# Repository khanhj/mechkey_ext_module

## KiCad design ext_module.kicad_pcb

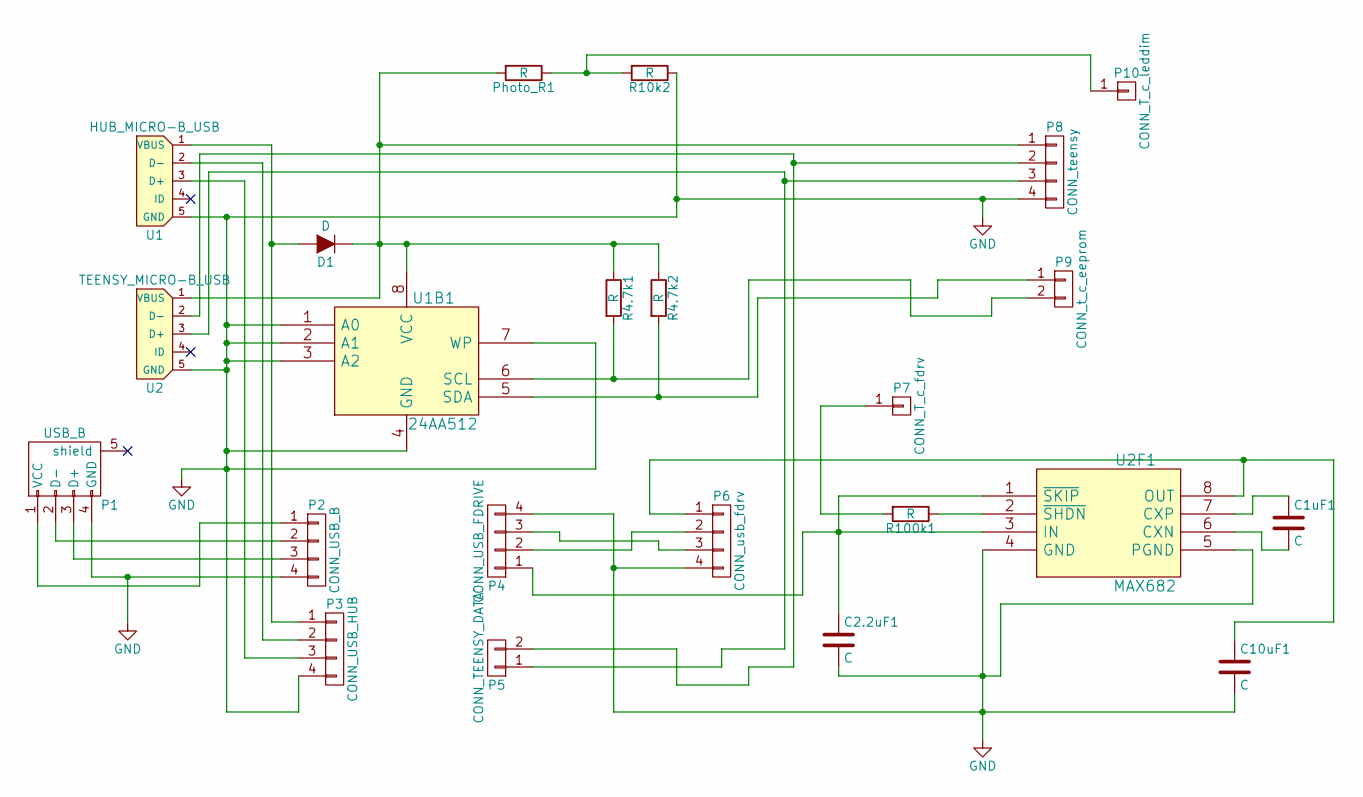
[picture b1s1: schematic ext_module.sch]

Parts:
C1uF1, C2.2uF1, C10uF1: C; C_0805
D1: D; D_A-405_P7.62mm_Horizontal
P1: USB_B; USB_A
P2: CONN_USB_B; Pin_Header_Straight_1x04_Pitch2.54mm
P3: CONN_USB_HUB; Pin_Header_Straight_1x04_Pitch2.54mm
P4: CONN_USB_FDRIVE; Pin_Header_Straight_1x04_Pitch2.54mm
P5: CONN_TEENSY_DATA; Pin_Header_Straight_1x02_Pitch2.54mm
P6: CONN_usb_fdrv; Pin_Header_Straight_1x04_Pitch2.54mm
P7: CONN_T_c_fdrv; Pin_Header_Straight_1x01_Pitch2.54mm
P8: CONN_teensy; Pin_Header_Straight_1x04_Pitch2.54mm
P9: CONN_t_c_eeprom; Pin_Header_Straight_1x02_Pitch2.54mm
P10: CONN_T_c_leddim; Pin_Header_Straight_1x01_Pitch2.54mm
Photo_R1: R; Pin_Header_Angled_1x02_Pitch2.54mm
R4.7k1, R4.7k2, R10k2, R100k1: R; R_0805
U1: HUB_MICRO-B_USB; USB_Micro-B
U1B1: 24AA512; SOIC-8-N
U2: TEENSY_MICRO-B_USB; USB_Micro-B
U2F1: MAX682; SOIC-8-N

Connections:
GND: C2.2uF1.2, C10uF1.2, P1.4 (GND), P2.4, P3.4, P4.4, P6.4, P8.4, R10k2.1, U1.5 (GND), U1B1.1 (A0), U1B1.2 (A1), U1B1.3 (A2), U1B1.4 (GND), U1B1.7 (WP), U2.5 (GND), U2F1.4 (GND), U2F1.5 (PGND)
unnamed: C1uF1.1, U2F1.7 (CXP)
unnamed: C1uF1.2, U2F1.6 (CXN)
unnamed: C2.2uF1.1, P4.1, U2F1.1 (~SKIP), U2F1.3 (IN)
unnamed: C10uF1.1, P6.1, U2F1.8 (OUT)
unnamed: D1.1 (K), P8.1, Photo_R1.2, R4.7k1.1, R4.7k2.1, U1B1.8 (VCC), U2.1 (VBUS)
unnamed: D1.2 (A), P3.1, U1.1 (VBUS)
unnamed: P1.1 (VCC), P2.1
unnamed: P1.2 (D-), P2.2
unnamed: P1.3 (D+), P2.3
unnamed: P3.2, U1.2 (D-)
unnamed: P3.3, U1.3 (D+)
unnamed: P4.2, P6.2
unnamed: P4.3, P6.3
unnamed: P5.1, P8.3, U2.3 (D+)
unnamed: P5.2, P8.2, U2.2 (D-)
unnamed: P7.1, R100k1.2
unnamed: P9.1, R4.7k2.2, U1B1.5 (SDA)
unnamed: P9.2, R4.7k1.2, U1B1.6 (SCL)
unnamed: P10.1, Photo_R1.1, R10k2.2
unnamed: R100k1.1, U2F1.2 (~SHDN)

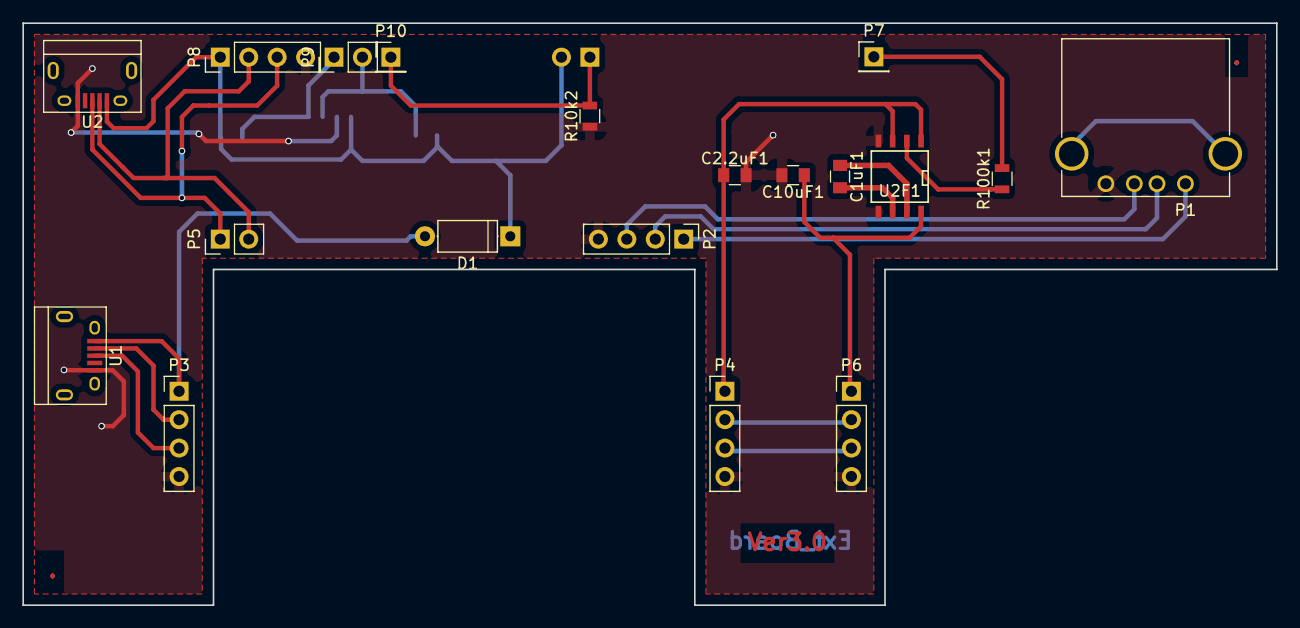
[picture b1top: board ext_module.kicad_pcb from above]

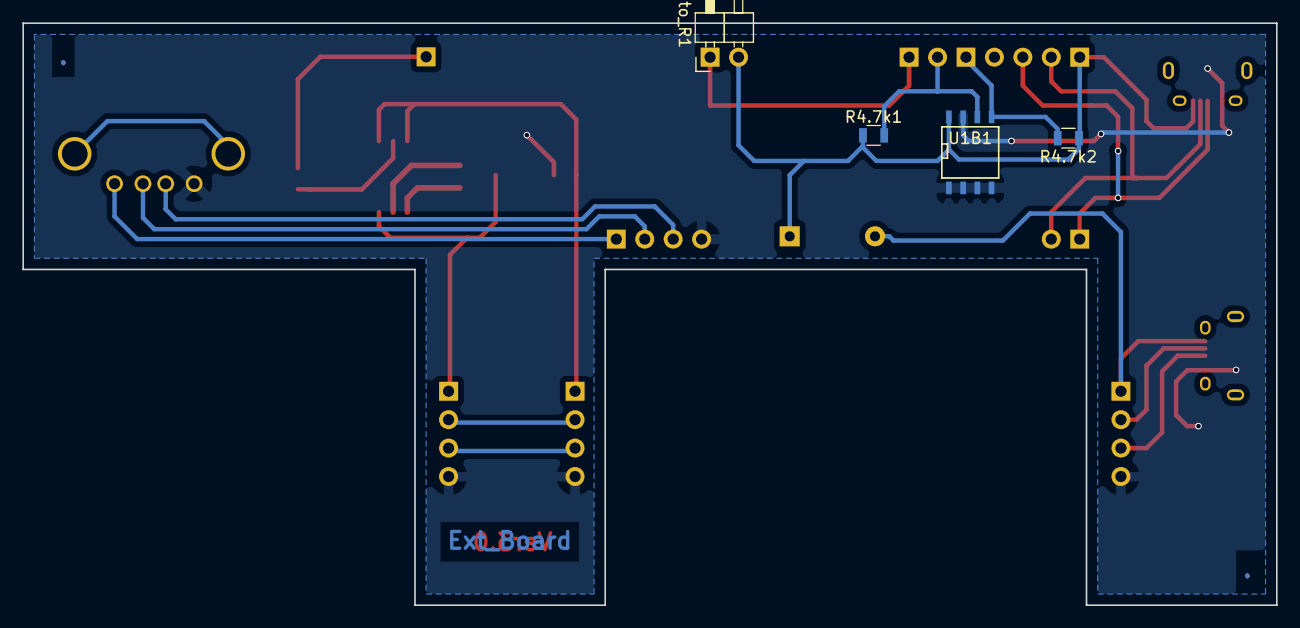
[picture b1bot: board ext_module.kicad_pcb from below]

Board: 2 copper layers, 112.0 x 52.0 mm, 23 parts (4 on the bottom side), 21 nets.

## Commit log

2018-10-18 complete
2018-11-18 tweak ext mod
2018-11-21 count distance
